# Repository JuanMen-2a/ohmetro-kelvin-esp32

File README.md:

# Óhmetro Kelvin de 4 Hilos — ESP32 + MQTT + Android

> Trabajo Final — Diseño Electrónico, UIS 2026-II

Instrumento de medición de resistencias de bajo valor (rango: miliohmios) basado en el método Kelvin de 4 hilos. El ESP32 adquiere la señal, la procesa y la transmite vía MQTT a una app Android en tiempo real.

---

## Arquitectura del sistema
Circuito Kelvin → ESP32 → Hotspot celular → Internet → test.mosquitto.org → Internet → App Android

---

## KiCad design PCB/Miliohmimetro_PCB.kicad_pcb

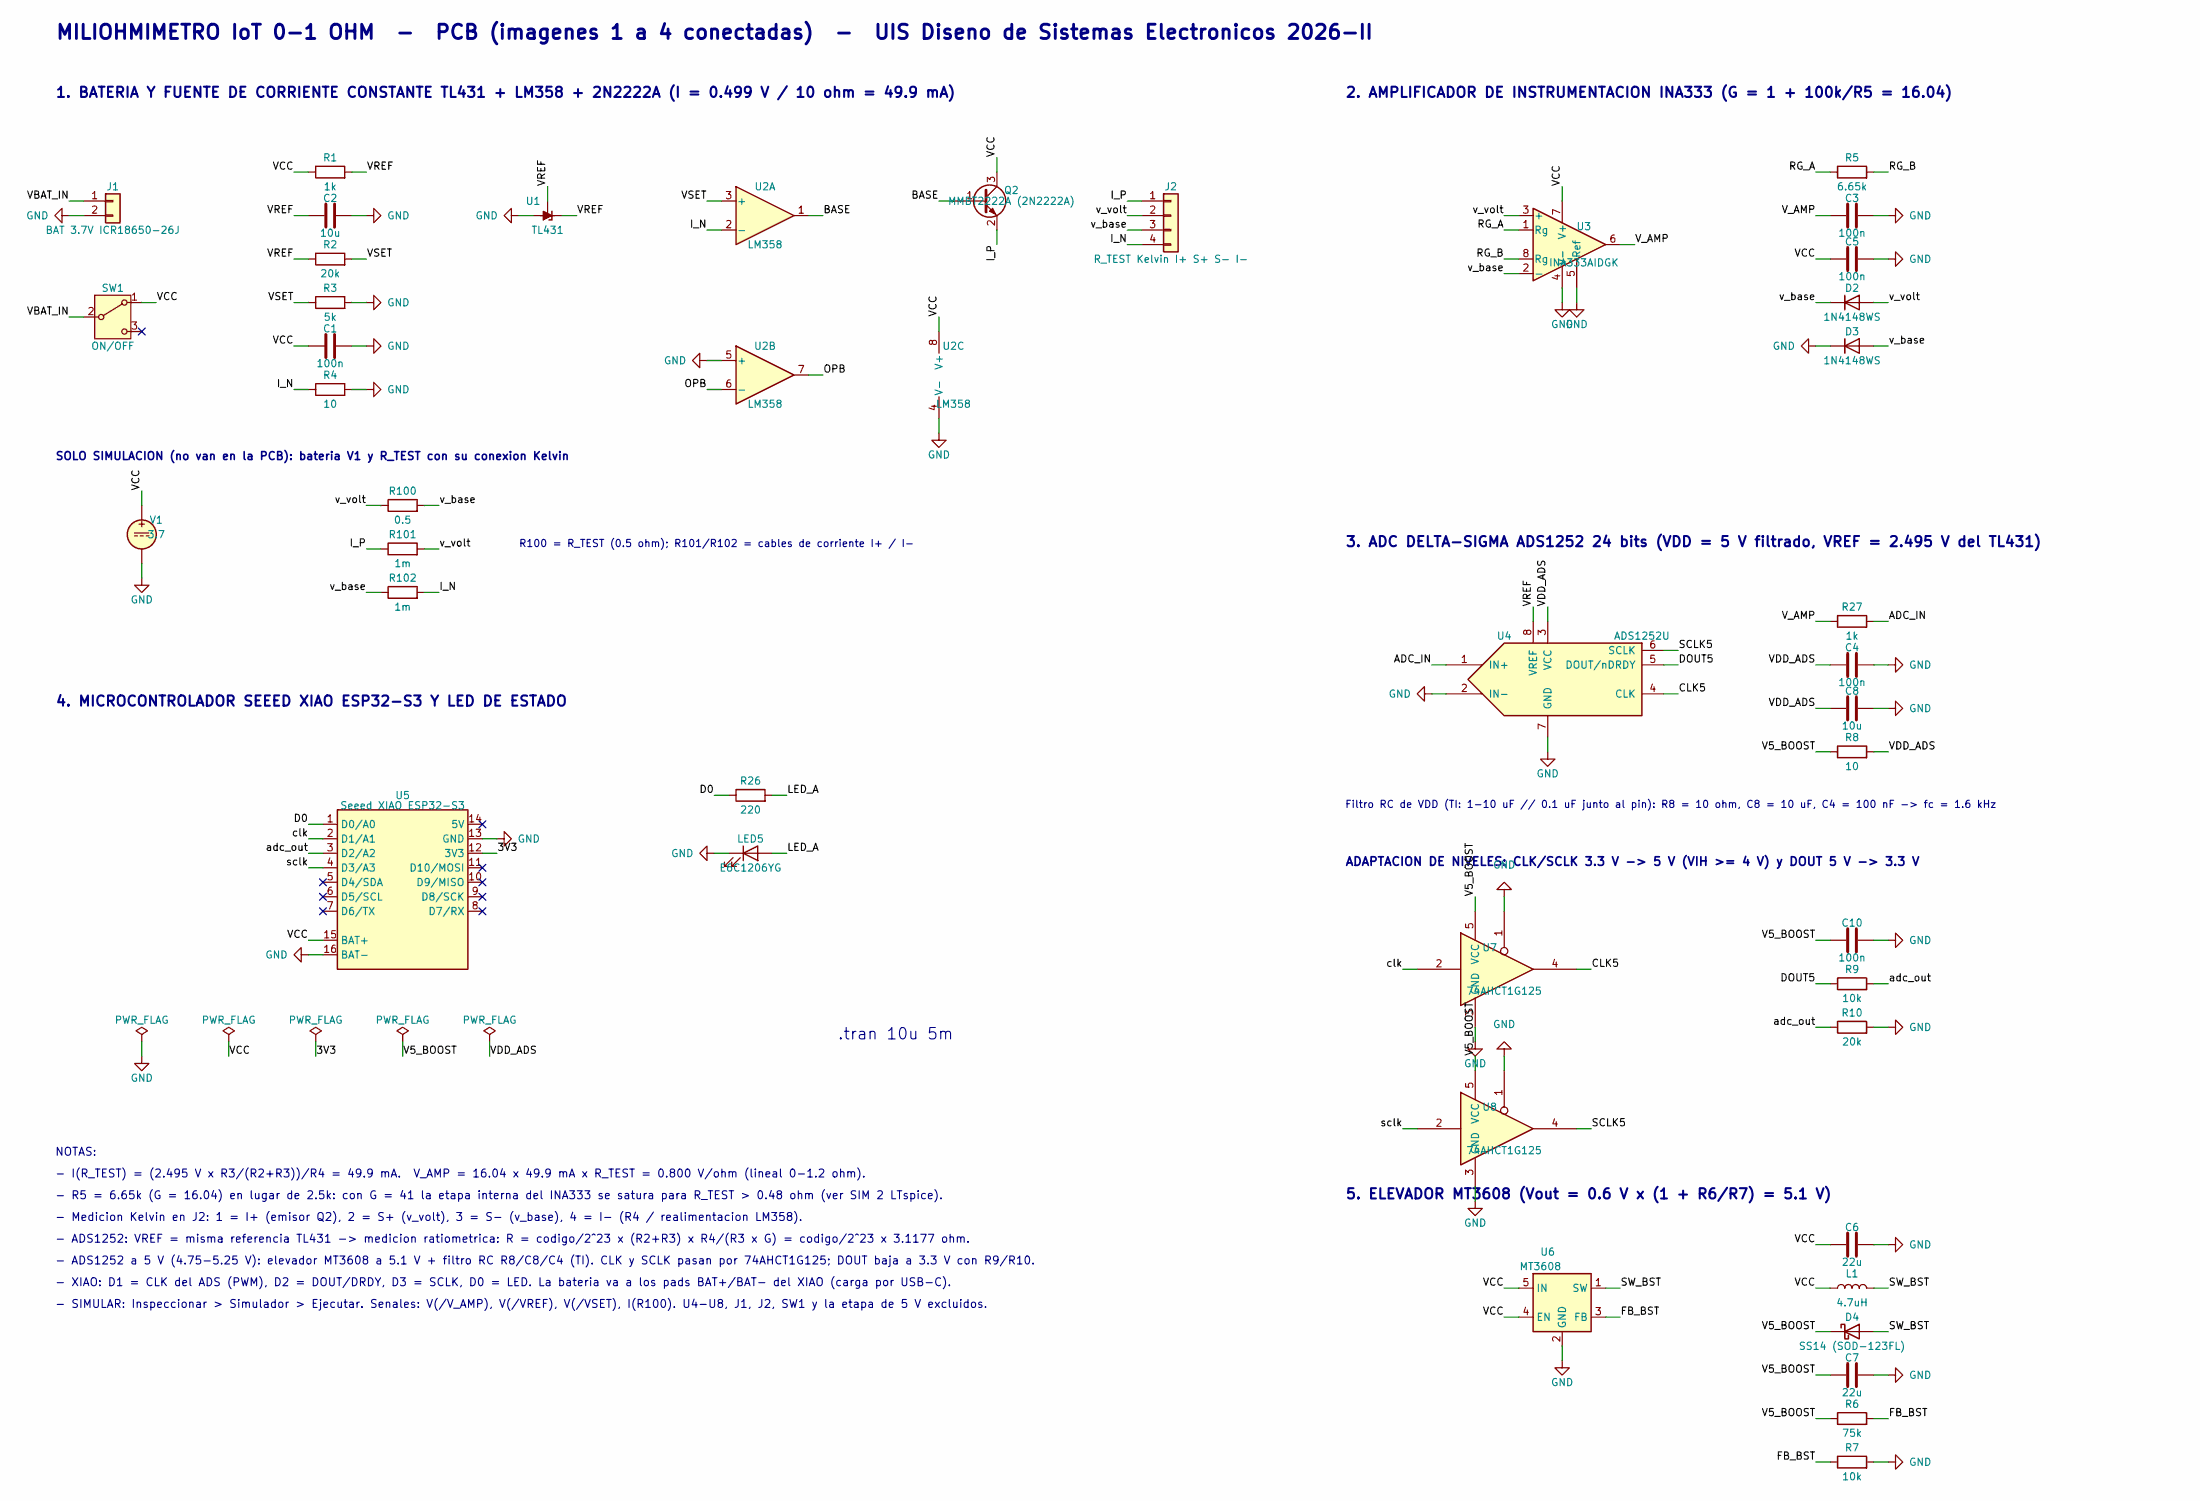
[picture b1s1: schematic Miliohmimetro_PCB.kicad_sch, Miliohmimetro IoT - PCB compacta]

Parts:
C1, C3, C4, C5, C10: 100n; C_0603_1608Metric
C2, C8: 10u; C_0805_2012Metric
C6, C7: 22u; C_0805_2012Metric
D2, D3: 1N4148WS; D_SOD-323
D4: SS14 (SOD-123FL); D_SOD-123F
J1: BAT 3.7V ICR18650-26J; JST_PH_B2B-PH-K_1x02_P2.00mm_Vertical
J2: R_TEST Kelvin I+ S+ S- I-; JST_PH_B4B-PH-K_1x04_P2.00mm_Vertical
L1: 4.7uH; L_Taiyo-Yuden_NR-30xx
LED5: E6C1206YG; LED_1206_3216Metric
Q2: MMBT2222A (2N2222A); SOT-23
R1, R27: 1k; R_0603_1608Metric
R2, R10: 20k; R_0603_1608Metric
R3: 5k; R_0603_1608Metric
R4: 10; R_0805_2012Metric
R5: 6.65k; R_0603_1608Metric
R6: 75k; R_0603_1608Metric
R7, R9: 10k; R_0603_1608Metric
R8: 10; R_0603_1608Metric
R26: 220; R_0603_1608Metric
R100: 0.5
R101, R102: 1m
SW1: ON/OFF; SW_SPDT_PCM12
U1: TL431; SOT-23
U2: LM358; SOIC-8_3.9x4.9mm_P1.27mm
U3: INA333AIDGK; VSSOP-8_3x3mm_P0.65mm
U4: ADS1252U; SOIC-8_3.9x4.9mm_P1.27mm
U5: Seeed XIAO ESP32-S3; Seeed_XIAO_ESP32S3_THT
U6: MT3608; SOT-23-6
U7, U8: 74AHCT1G125; SOT-23-5
V1: 3.7

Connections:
/3V3: U5.12 (3V3)
/ADC_IN: R27.2, U4.1 (IN+)
/BASE: Q2.1 (B), U2.1
/CLK5: U4.4 (CLK), U7.4
/D0: R26.1, U5.1 (D0/A0)
/DOUT5: R9.1, U4.5 (DOUT/nDRDY)
/FB_BST: R6.2, R7.1, U6.3 (FB)
/I_N: J2.4, R4.1, R102.2, U2.2 (-)
/I_P: J2.1, Q2.2 (E), R101.1
/LED_A: LED5.2 (A), R26.2
/OPB: U2.6 (-), U2.7
/RG_A: R5.1, U3.1 (Rg)
/RG_B: R5.2, U3.8 (Rg)
/SCLK5: U4.6 (SCLK), U8.4
/SW_BST: D4.2 (A), L1.2, U6.1 (SW)
/V5_BOOST: C7.1, C10.1, D4.1 (K), R6.1, R8.1, U7.5 (VCC), U8.5 (VCC)
/VBAT_IN: J1.1, SW1.2 (B)
/VCC: C1.1, C5.1, C6.1, L1.1, Q2.3 (C), R1.1, SW1.1 (A), U2.8 (V+), U3.7 (V+), U5.15 (BAT+), U6.4 (EN), U6.5 (IN), V1.1
/VDD_ADS: C4.1, C8.1, R8.2, U4.3 (VCC)
/VREF: C2.1, R1.2, R2.1, U1.1 (K), U1.2 (REF), U4.8 (VREF)
/VSET: R2.2, R3.1, U2.3 (+)
/V_AMP: C3.1, R27.1, U3.6
/adc_out: R9.2, R10.1, U5.3 (D2/A2)
/clk: U5.2 (D1/A1), U7.2
/sclk: U5.4 (D3/A3), U8.2
/v_base: D2.1 (K), D3.2 (A), J2.3, R100.2, R102.1, U3.2 (-)
/v_volt: D2.2 (A), J2.2, R100.1, R101.2, U3.3 (+)
GND: C1.2, C2.2, C3.2, C4.2, C5.2, C6.2, C7.2, C8.2, C10.2, D3.1 (K), J1.2, LED5.1 (K), R3.2, R4.2, R7.2, R10.2, U1.3 (A), U2.4 (V-), U2.5 (+), U3.4 (V-), U3.5 (Ref), U4.2 (IN-), U4.7 (GND), U5.13 (GND), U5.16 (BAT-), U6.2 (GND), U7.1, U7.3 (GND), U8.1, U8.3 (GND), V1.2

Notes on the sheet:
MILIOHMIMETRO IoT 0-1 OHM - PCB (imagenes 1 a 4 conectadas) - UIS Diseno de Sistemas Electronicos 2026-II
1. BATERIA Y FUENTE DE CORRIENTE CONSTANTE TL431 + LM358 + 2N2222A (I = 0.499 V / 10 ohm = 49.9 mA)
SOLO SIMULACION (no van en la PCB): bateria V1 y R_TEST con su conexion Kelvin
R100 = R_TEST (0.5 ohm); R101/R102 = cables de corriente I+ / I-
2. AMPLIFICADOR DE INSTRUMENTACION INA333 (G = 1 + 100k/R5 = 16.04)
3. ADC DELTA-SIGMA ADS1252 24 bits (VDD = 5 V filtrado, VREF = 2.495 V del TL431)
Filtro RC de VDD (TI: 1-10 uF // 0.1 uF junto al pin): R8 = 10 ohm, C8 = 10 uF, C4 = 100 nF -> fc = 1.6 kHz
ADAPTACION DE NIVELES: CLK/SCLK 3.3 V -> 5 V (VIH >= 4 V) y DOUT 5 V -> 3.3 V
5. ELEVADOR MT3608 (Vout = 0.6 V x (1 + R6/R7) = 5.1 V)
4. MICROCONTROLADOR SEEED XIAO ESP32-S3 Y LED DE ESTADO
.tran 10u 5m
NOTAS:
- I(R_TEST) = (2.495 V x R3/(R2+R3))/R4 = 49.9 mA. V_AMP = 16.04 x 49.9 mA x R_TEST = 0.800 V/ohm (lineal 0-1.2 ohm).
- R5 = 6.65k (G = 16.04) en lugar de 2.5k: con G = 41 la etapa interna del INA333 se satura para R_TEST > 0.48 ohm (ver SIM 2 LTspice).
- Medicion Kelvin en J2: 1 = I+ (emisor Q2), 2 = S+ (v_volt), 3 = S- (v_base), 4 = I- (R4 / realimentacion LM358).
- ADS1252: VREF = misma referencia TL431 -> medicion ratiometrica: R = codigo/2^23 x (R2+R3) x R4/(R3 x G) = codigo/2^23 x 3.1177 ohm.
- ADS1252 a 5 V (4.75-5.25 V): elevador MT3608 a 5.1 V + filtro RC R8/C8/C4 (TI). CLK y SCLK pasan por 74AHCT1G125; DOUT baja a 3.3 V con R9/R10.
- XIAO: D1 = CLK del ADS (PWM), D2 = DOUT/DRDY, D3 = SCLK, D0 = LED. La bateria va a los pads BAT+/BAT- del XIAO (carga por USB-C).
- SIMULAR: Inspeccionar > Simulador > Ejecutar. Senales: V(/V_AMP), V(/VREF), V(/VSET), I(R100). U4-U8, J1, J2, SW1 y la etapa de 5 V excluidos.

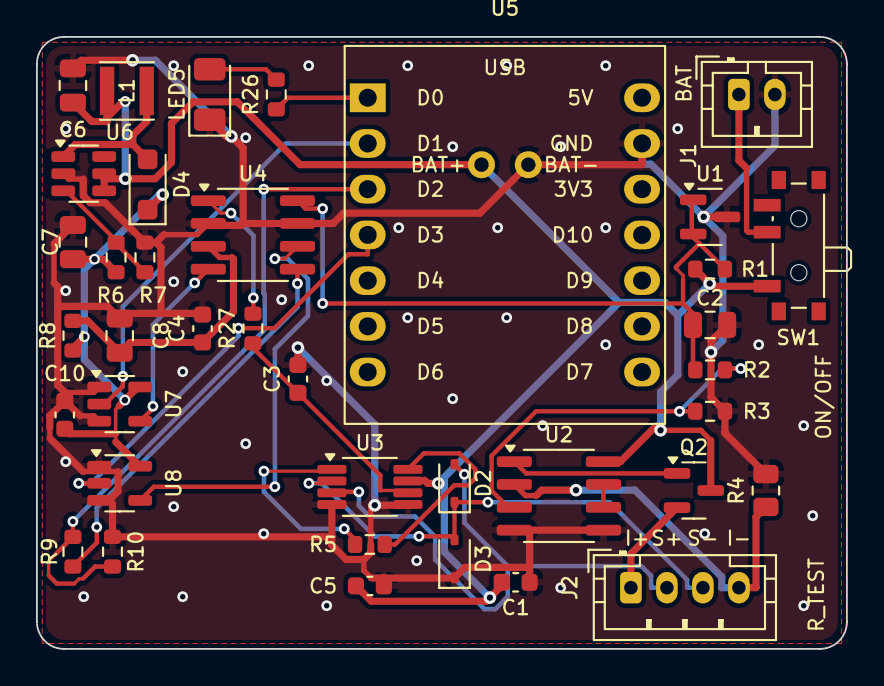
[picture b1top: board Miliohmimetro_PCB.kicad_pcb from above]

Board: 2 copper layers, 45.0 x 34.0 mm, 38 parts (0 on the bottom side), 27 nets.
